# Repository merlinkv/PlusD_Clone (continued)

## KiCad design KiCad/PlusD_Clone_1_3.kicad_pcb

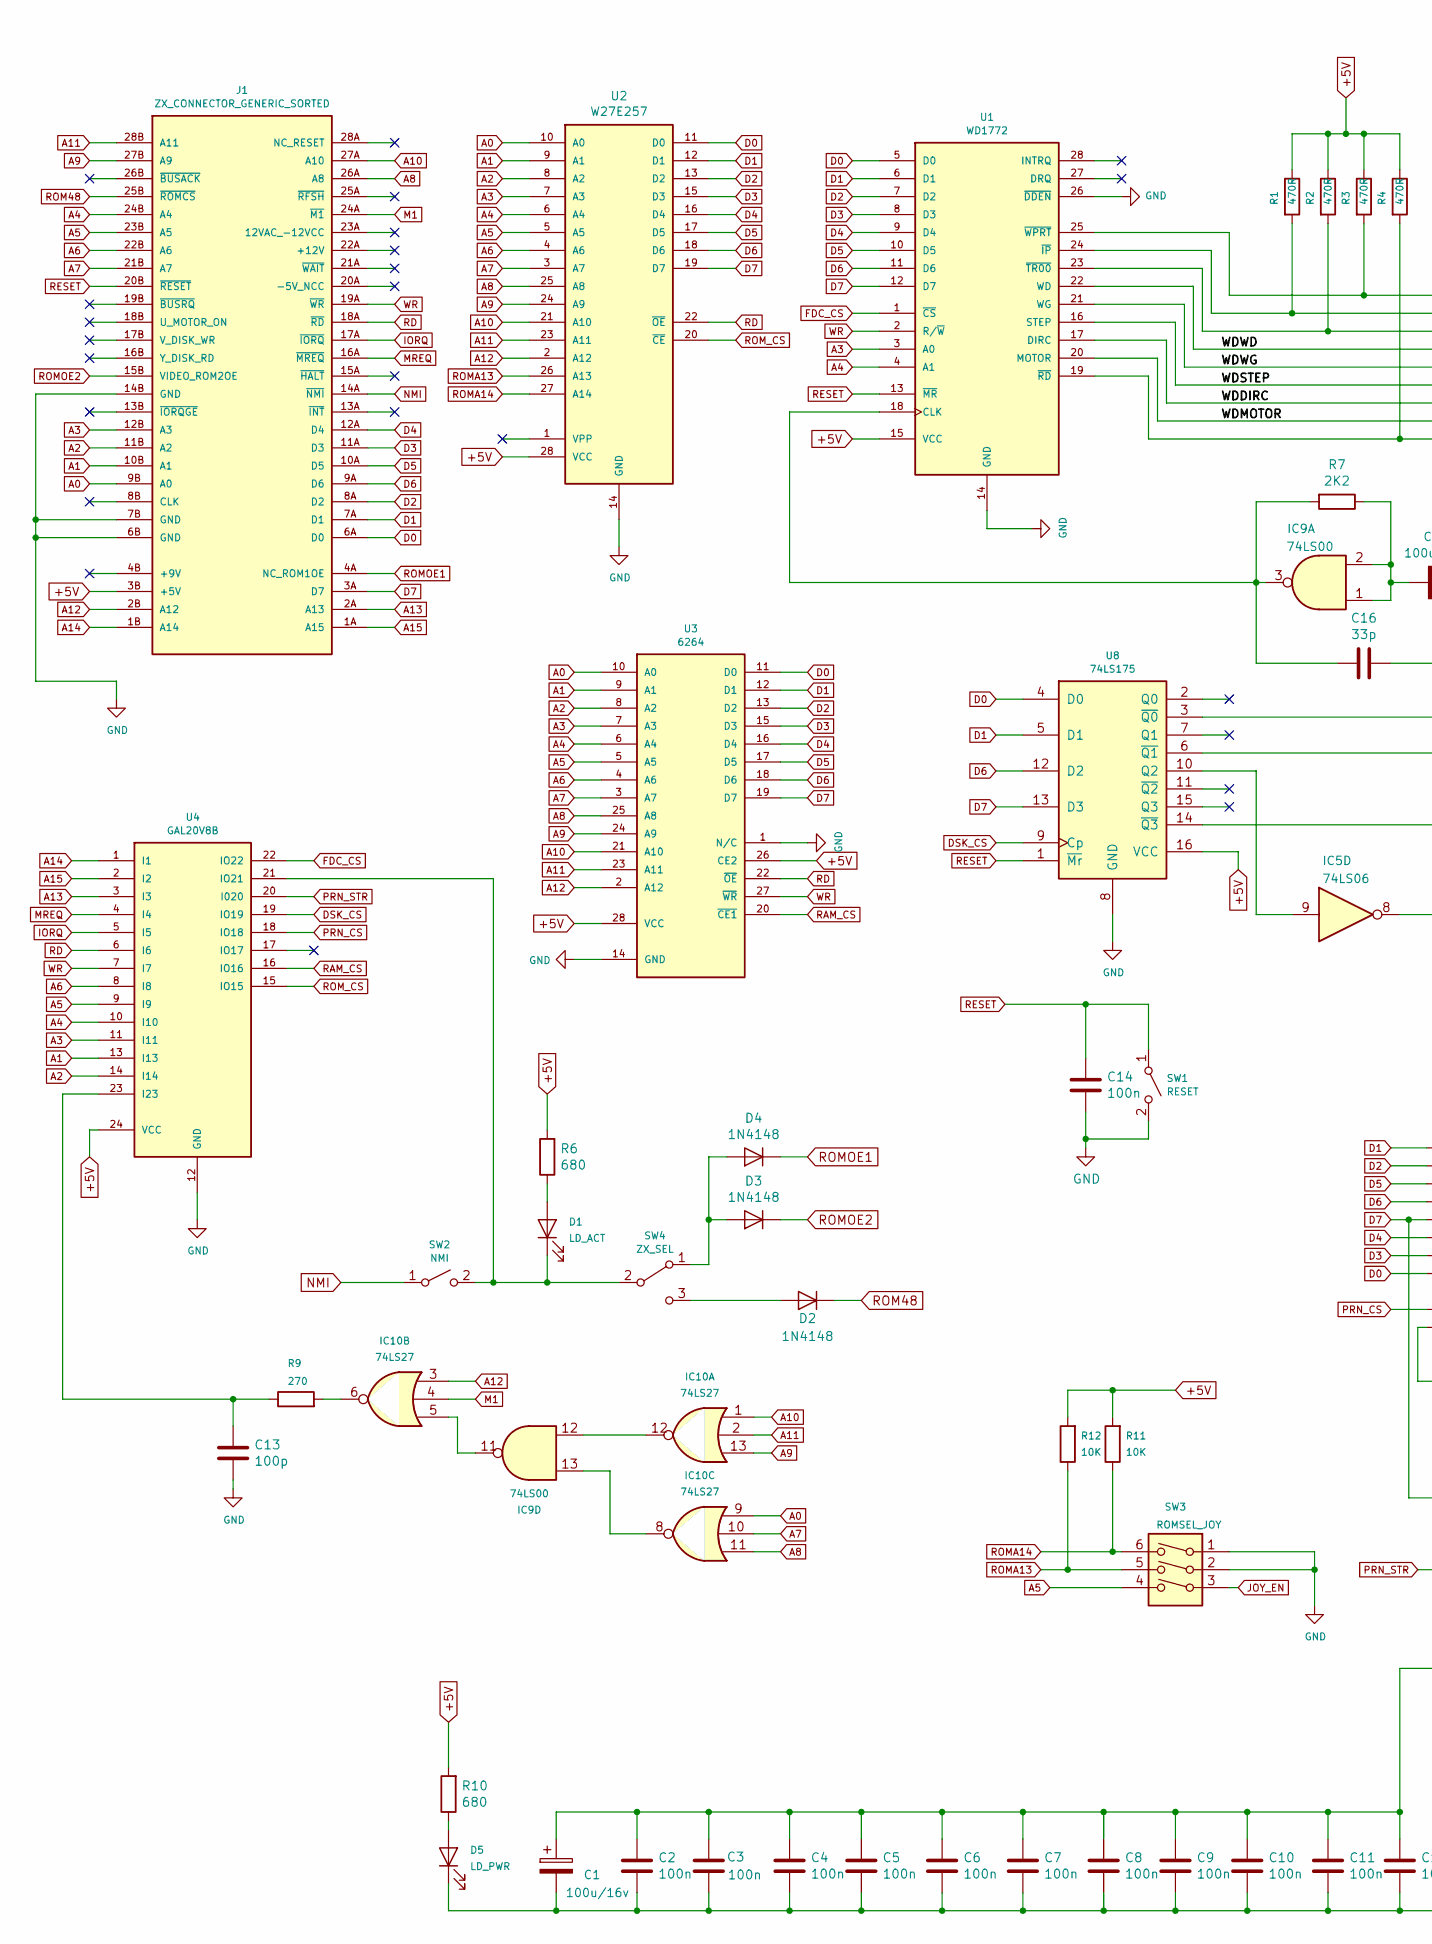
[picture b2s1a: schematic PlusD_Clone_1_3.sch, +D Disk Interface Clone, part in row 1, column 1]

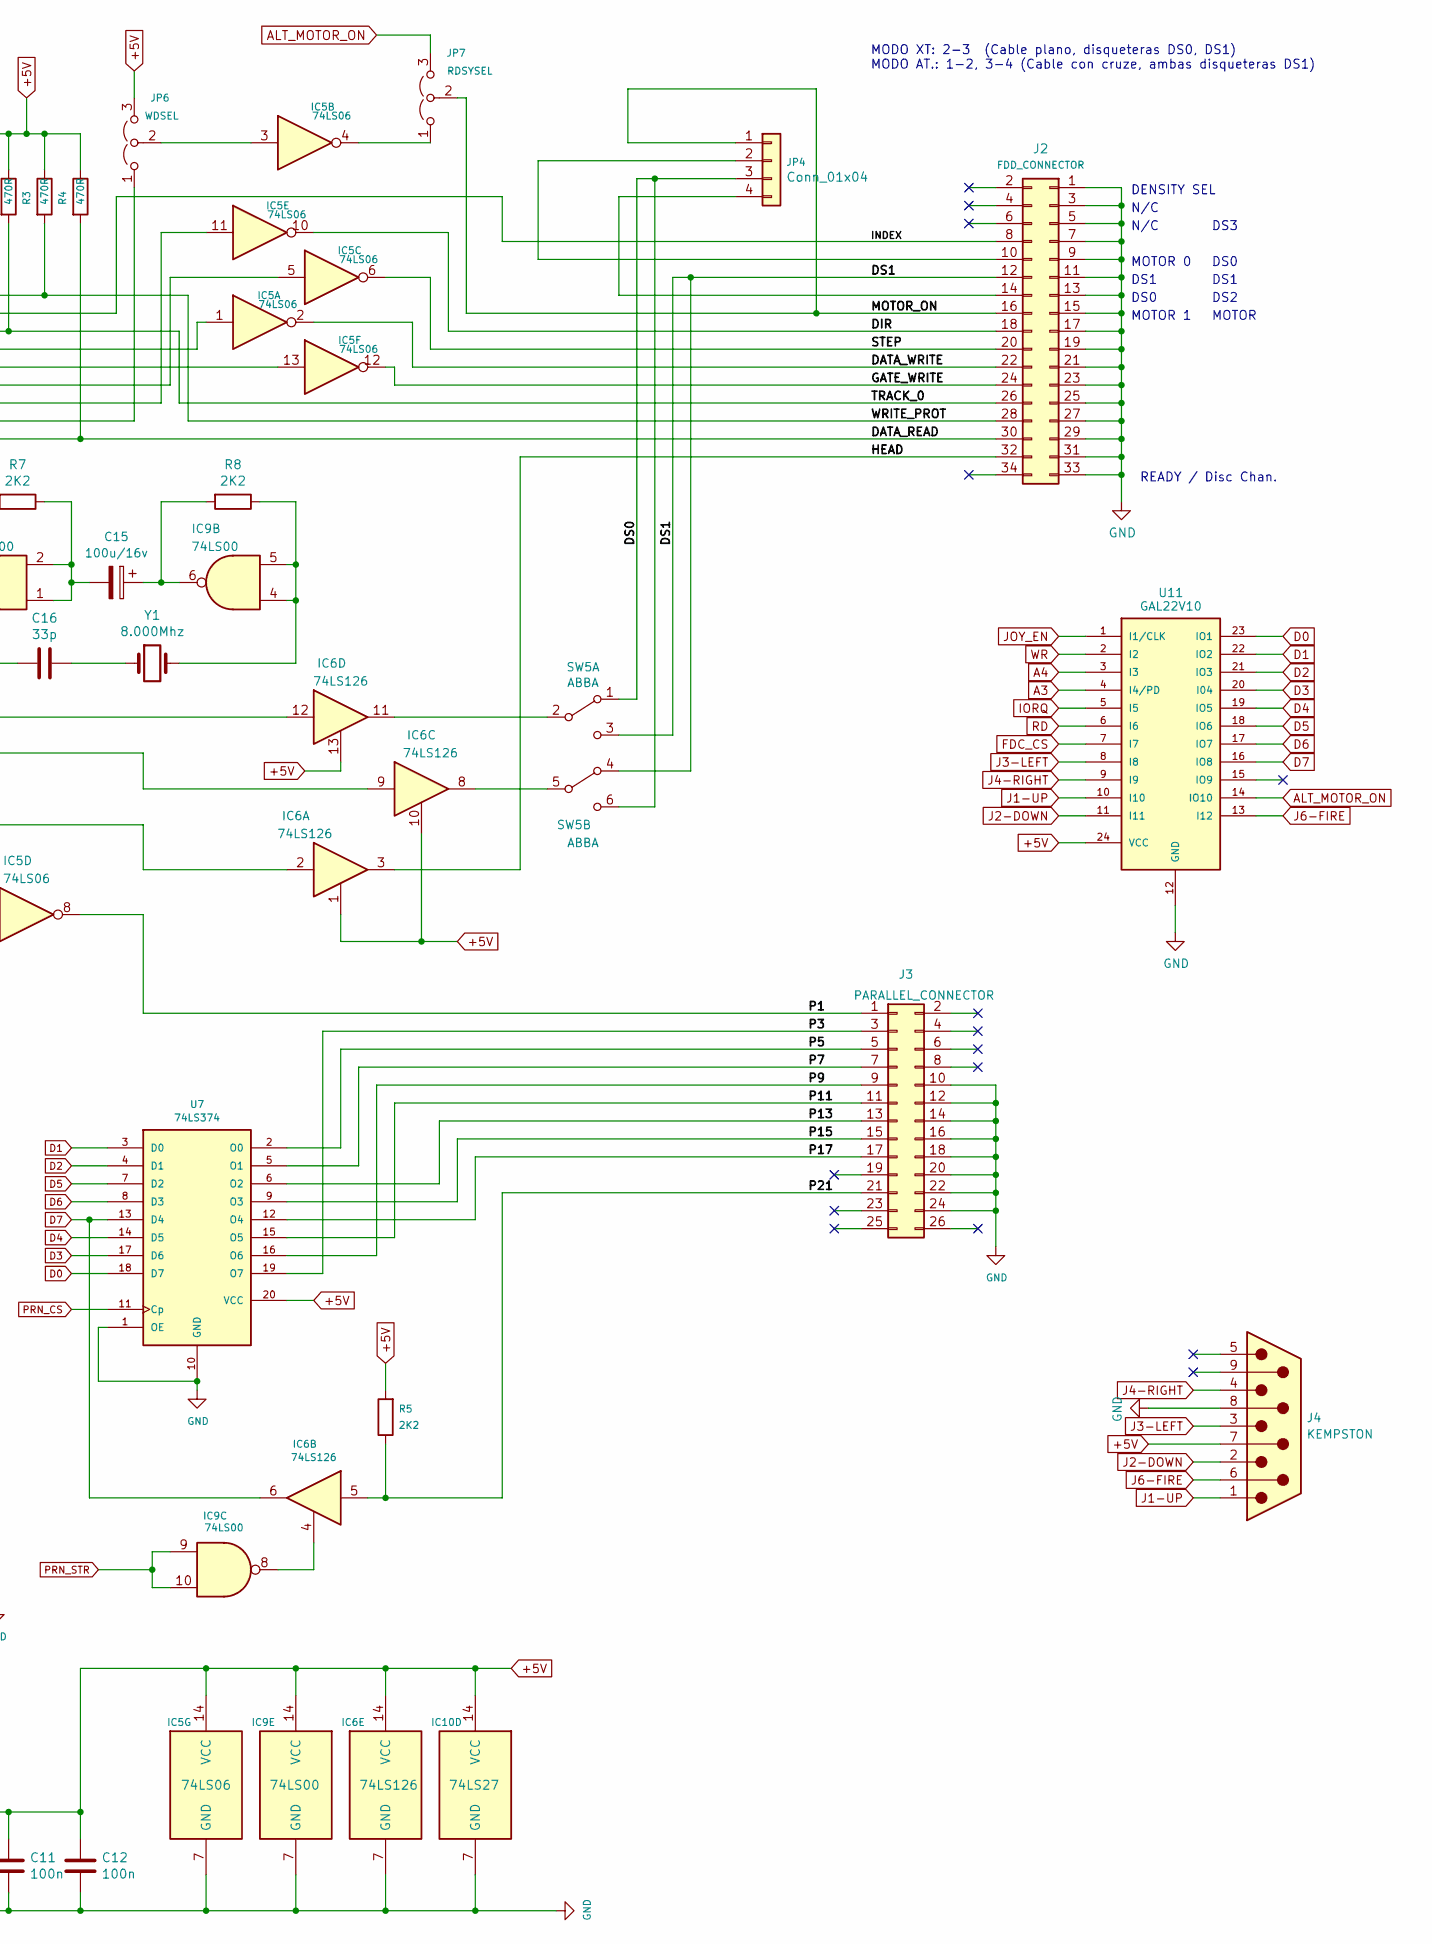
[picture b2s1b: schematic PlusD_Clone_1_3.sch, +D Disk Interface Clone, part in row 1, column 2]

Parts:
C1, C15: 100u/16v; C_Elec_6.3x5.4
C2, C3, C4, C5, C6, C7, C8, C9, C10, C11, C12, C14: 100n; C_Disc_D5.0mm_W2.5mm_P5.00mm
C13: 100p; C_Disc_D5.0mm_W2.5mm_P5.00mm
C16: 33p; C_Disc_D5.0mm_W2.5mm_P5.00mm
D1: LD_ACT; LED_D5.0mm
D2, D3, D4: 1N4148; D_DO-35_SOD27_P7.62mm_Horizontal
D5: LD_PWR; LED_D5.0mm
IC5: 74LS06; DIP-14_W7.62mm_Socket_LongPads
IC6: 74LS126; DIP-14_W7.62mm_Socket_LongPads
IC9: 74LS00; DIP-14_W7.62mm_Socket_LongPads
IC10: 74LS27; DIP-14_W7.62mm_Socket_LongPads
J1: ZX_CONNECTOR_GENERIC_SORTED
J2: FDD_CONNECTOR; PinHeader_2x17_P2.54mm_Vertical
J3: PARALLEL_CONNECTOR; PinHeader_2x13_P2.54mm_Vertical
J4: KEMPSTON; DSUB-9_Male_Horizontal_P2.77x2.84mm_EdgePinOffset4.94mm_Hou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
JP4: Conn_01x04; PinHeader_1x04_P2.54mm_Horizontal
JP6: WDSEL; SolderJumper-3_P1.3mm_Open_RoundedPad1.0x1.5mm
JP7: RDSYSEL; SolderJumper-3_P1.3mm_Open_RoundedPad1.0x1.5mm
R1, R2, R3, R4: 470R; R_Axial_DIN0207_L6.3mm_D2.5mm_P7.62mm_Horizontal
R5, R7, R8: 2K2; R_Axial_DIN0207_L6.3mm_D2.5mm_P7.62mm_Horizontal
R6, R10: 680; R_Axial_DIN0207_L6.3mm_D2.5mm_P7.62mm_Horizontal
R9: 270; R_Axial_DIN0207_L6.3mm_D2.5mm_P7.62mm_Horizontal
R11, R12: 10K; R_Axial_DIN0207_L6.3mm_D2.5mm_P7.62mm_Horizontal
SW1: RESET; SW_PUSH_6mm
SW2: NMI; SW_PUSH_6mm
SW3: ROMSEL_JOY; SW_DIP_SPSTx03_Piano_10.8x9.18mm_W7.62mm_P2.54mm
SW4: ZX_SEL; SW_CuK_OS102011MA1QN1_SPDT_Angled
SW5: ABBA; SW_CuK_JS202011AQN_DPDT_Angled
U1: WD1772; DIP-28_W15.24mm_Socket_LongPads
U2: W27E257; DIP-28_W15.24mm_Socket_LongPads
U3: 6264; DIP-28_W15.24mm_Socket_LongPads
U4: GAL20V8B; DIP-24_W7.62mm_Socket_LongPads
U7: 74LS374; DIP-20_W7.62mm_Socket_LongPads
U8: 74LS175; DIP-16_W7.62mm_Socket_LongPads
U11: GAL22V10; DIP-24_W7.62mm_Socket_LongPads
Y1: 8.000Mhz; Crystal_HC18-U_Vertical

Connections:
+5V: C1.1, C2.2, C3.2, C4.2, C5.2, C6.2, C7.2, C8.2, C9.2, C10.2, C11.2, C12.2, IC5.14 (VCC), IC6.1, IC6.10, IC6.13, IC6.14 (VCC), IC9.14 (VCC), IC10.14 (VCC), J1.3B (+5V), J4.7, JP6.3 (B), R1.1, R2.1, R3.1, R4.1, R5.2, R6.2, R10.2, R11.2, R12.2, U1.15 (VCC), U2.28 (VCC), U3.26 (CE2), U3.28 (VCC), U4.24 (VCC), U7.20 (VCC), U8.16 (VCC), U11.24 (VCC)
/DATA_READ: J2.30, R4.2, U1.19 (~RD)
/DATA_WRITE: IC5.2, J2.22
/DIR: IC5.10, J2.18
/DS0: JP4.3, SW5.1 (A), SW5.6 (C)
/DS1: J2.12, SW5.3 (C), SW5.4 (A)
/GATE_WRITE: IC5.12, J2.24
/HEAD: IC6.3, J2.32
/INDEX: J2.8, R1.2, U1.24 (~IP)
/MOTOR_ON: J2.16, JP4.1, JP7.2 (C)
/P1: IC5.8, J3.1
/P3: J3.3, U7.19 (O7)
/P5: J3.5, U7.2 (O0)
/P7: J3.7, U7.5 (O1)
/P9: J3.9, U7.16 (O6)
/P11: J3.11, U7.15 (O5)
/P13: J3.13, U7.6 (O2)
/P15: J3.15, U7.9 (O3)
/P17: J3.17, U7.12 (O4)
/P21: IC6.5, J3.21, R5.1
/STEP: IC5.6, J2.20
/TRACK_0: J2.26, R2.2, U1.23 (~TR00)
/WDDIRC: IC5.11, U1.17 (DIRC)
/WDMOTOR: JP6.1 (A), U1.20 (MOTOR)
/WDSTEP: IC5.5, U1.16 (STEP)
/WDWD: IC5.1, U1.22 (WD)
/WDWG: IC5.13, U1.21 (WG)
/WRITE_PROT: J2.28, R3.2, U1.25 (~WPRT)
A0: IC10.9, J1.9B (A0), U2.10 (A0), U3.10 (A0)
A1: J1.10B (A1), U2.9 (A1), U3.9 (A1), U4.13 (I13)
A2: J1.11B (A2), U2.8 (A2), U3.8 (A2), U4.14 (I14)
A3: J1.12B (A3), U1.3 (A0), U2.7 (A3), U3.7 (A3), U4.11 (I11), U11.4 (I4/PD)
A4: J1.24B (A4), U1.4 (A1), U2.6 (A4), U3.6 (A4), U4.10 (I10), U11.3 (I3)
A5: J1.23B (A5), SW3.4, U2.5 (A5), U3.5 (A5), U4.9 (I9)
A6: J1.22B (A6), U2.4 (A6), U3.4 (A6), U4.8 (I8)
A7: IC10.10, J1.21B (A7), U2.3 (A7), U3.3 (A7)
A8: IC10.11, J1.26A (A8), U2.25 (A8), U3.25 (A8)
A9: IC10.13, J1.27B (A9), U2.24 (A9), U3.24 (A9)
A10: IC10.1, J1.27A (A10), U2.21 (A10), U3.21 (A10)
A11: IC10.2, J1.28B (A11), U2.23 (A11), U3.23 (A11)
A12: IC10.3, J1.2B (A12), U2.2 (A12), U3.2 (A12)
A13: J1.2A (A13), U4.3 (I3)
A14: J1.1B (A14), U4.1 (I1)
A15: J1.1A (A15), U4.2 (I2)
ALT_MOTOR_ON: JP7.3 (B), U11.14 (IO10)
D0: J1.6A (D0), U1.5 (D0), U2.11 (D0), U3.11 (D0), U7.18 (D7), U8.4 (D0), U11.23 (IO1)
D1: J1.7A (D1), U1.6 (D1), U2.12 (D1), U3.12 (D1), U7.3 (D0), U8.5 (D1), U11.22 (IO2)
D2: J1.8A (D2), U1.7 (D2), U2.13 (D2), U3.13 (D2), U7.4 (D1), U11.21 (IO3)
D3: J1.11A (D3), U1.8 (D3), U2.15 (D3), U3.15 (D3), U7.17 (D6), U11.20 (I04)
D4: J1.12A (D4), U1.9 (D4), U2.16 (D4), U3.16 (D4), U7.14 (D5), U11.19 (IO5)
D5: J1.10A (D5), U1.10 (D5), U2.17 (D5), U3.17 (D5), U7.7 (D2), U11.18 (IO6)
D6: J1.9A (D6), U1.11 (D6), U2.18 (D6), U3.18 (D6), U7.8 (D3), U8.12 (D2), U11.17 (IO7)
D7: IC6.6, J1.3A (D7), U1.12 (D7), U2.19 (D7), U3.19 (D7), U7.13 (D4), U8.13 (D3), U11.16 (IO8)
DSK_CS: U4.19 (IO19), U8.9 (Cp)
FDC_CS: U1.1 (~CS), U4.22 (IO22), U11.7 (I7)
GND: C1.2, C2.1, C3.1, C4.1, C5.1, C6.1, C7.1, C8.1, C9.1, C10.1, C11.1, C12.1, C13.1, C14.1, D5.1 (K), IC5.7 (GND), IC6.7 (GND), IC9.7 (GND), IC10.7 (GND), J1.6B (GND), J1.7B (GND), J1.14B (GND), J2.1, J2.3, J2.5, J2.7, J2.9, J2.11, J2.13, J2.15, J2.17, J2.19, J2.21, J2.23, J2.25, J2.27, J2.29, J2.31, J2.33, J3.10, J3.12, J3.14, J3.16, J3.18, J3.20, J3.22, J3.24, J4.8, SW1.2 (B), SW3.1, SW3.2, U1.14 (GND), U1.26 (~DDEN), U2.14 (GND), U3.1 (N/C), U3.14 (GND), U4.12 (GND), U7.1 (OE), U7.10 (GND), U8.8 (GND), U11.12 (GND)
IORQ: J1.17A (~IORQ), U4.5 (I5), U11.5 (I5)
J1-UP: J4.1, U11.10 (I10)
J2-DOWN: J4.2, U11.11 (I11)
J3-LEFT: J4.3, U11.8 (I8)
J4-RIGHT: J4.4, U11.9 (I9)
J6-FIRE: J4.6, U11.13 (I12)
JOY_EN: SW3.3, U11.1 (I1/CLK)
M1: IC10.4, J1.24A (~M1)
MREQ: J1.16A (~MREQ), U4.4 (I4)
NMI: J1.14A (~NMI), SW2.1 (A)
unnamed: C13.2, R9.1, U4.23 (I23)
unnamed: C15.1, IC9.6, R8.2
unnamed: C15.2, IC9.1, IC9.2, R7.1
unnamed: C16.1, Y1.1
unnamed: C16.2, IC9.3, R7.2, U1.18 (CLK)
unnamed: D1.1 (K), SW2.2 (B), SW4.2 (B), U4.21 (IO21)
unnamed: D1.2 (A), R6.1
unnamed: D2.2 (A), SW4.3 (C)
unnamed: D3.2 (A), D4.2 (A), SW4.1 (A)
unnamed: D5.2 (A), R10.1
unnamed: IC5.3, JP6.2 (C)
unnamed: IC5.4, JP7.1 (A)
unnamed: IC5.9, U8.10 (Q2)
unnamed: IC6.2, U8.14 (~Q3)
unnamed: IC6.4, IC9.8
unnamed: IC6.8, SW5.5 (B)
unnamed: IC6.9, U8.6 (~Q1)
unnamed: IC6.11, SW5.2 (B)
unnamed: IC6.12, U8.3 (~Q0)
unnamed: IC9.4, IC9.5, R8.1, Y1.2
unnamed: IC9.11, IC10.5
unnamed: IC10.6, R9.2
unnamed: IC9.13, IC10.8
unnamed: IC9.12, IC10.12
unnamed: J2.10, JP4.2
unnamed: J2.14, JP4.4
PRN_CS: U4.18 (IO18), U7.11 (Cp)
PRN_STR: IC9.9, IC9.10, U4.20 (I020)
RAM_CS: U3.20 (~CE1), U4.16 (IO16)
RD: J1.18A (~RD), U2.22 (~OE), U3.22 (~OE), U4.6 (I6), U11.6 (I6)
RESET: C14.2, J1.20B (~RESET), SW1.1 (A), U1.13 (~MR), U8.1 (~Mr)
ROM48: D2.1 (K), J1.25B (~ROMCS)
ROMA13: R12.1, SW3.5, U2.26 (A13)
ROMA14: R11.1, SW3.6, U2.27 (A14)
ROMOE1: D4.1 (K), J1.4A (NC_ROM1OE)
ROMOE2: D3.1 (K), J1.15B (VIDEO_ROM2OE)
ROM_CS: U2.20 (~CE), U4.15 (IO15)
WR: J1.19A (~WR), U1.2 (R/~W), U3.27 (~WR), U4.7 (I7), U11.2 (I2)

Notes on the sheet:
READY / Disc Chan.
DENSITY SEL
N/C
MOTOR 1
DS0
DS1
MOTOR 0
MOTOR
DS2
DS0
DS3
MODO XT: 2-3 (Cable plano, disqueteras DS0, DS1) MODO AT.: 1-2, 3-4 (Cable con cruze, ambas disqueteras DS1)

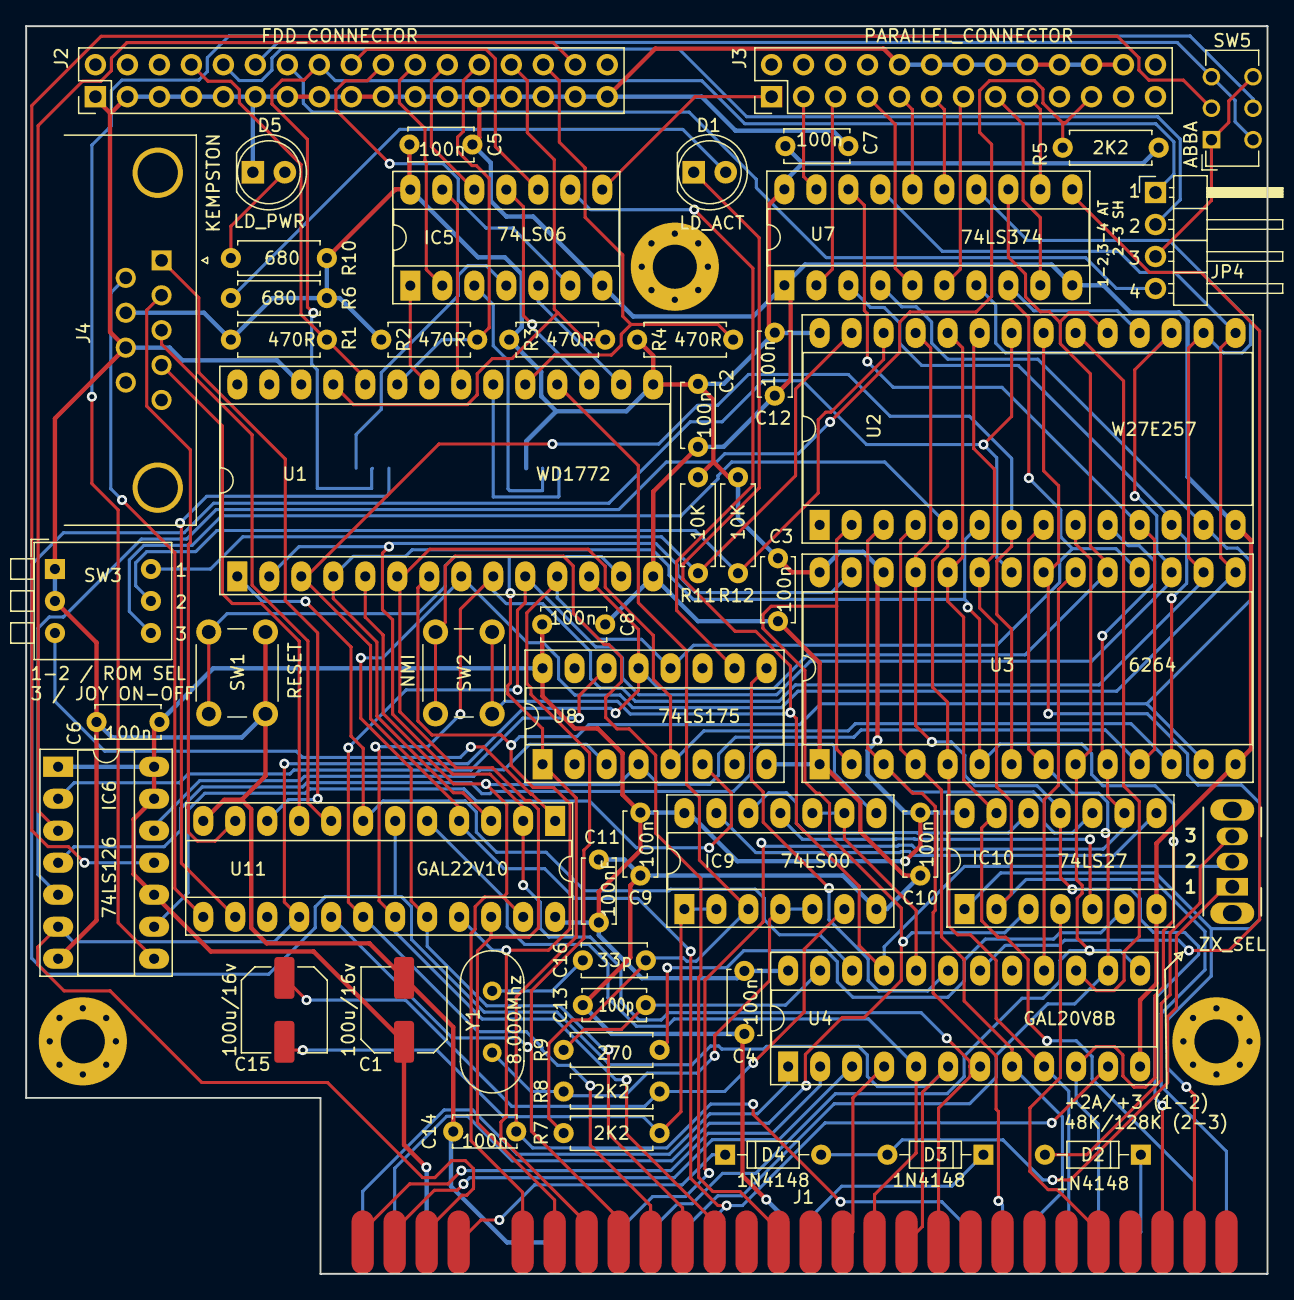
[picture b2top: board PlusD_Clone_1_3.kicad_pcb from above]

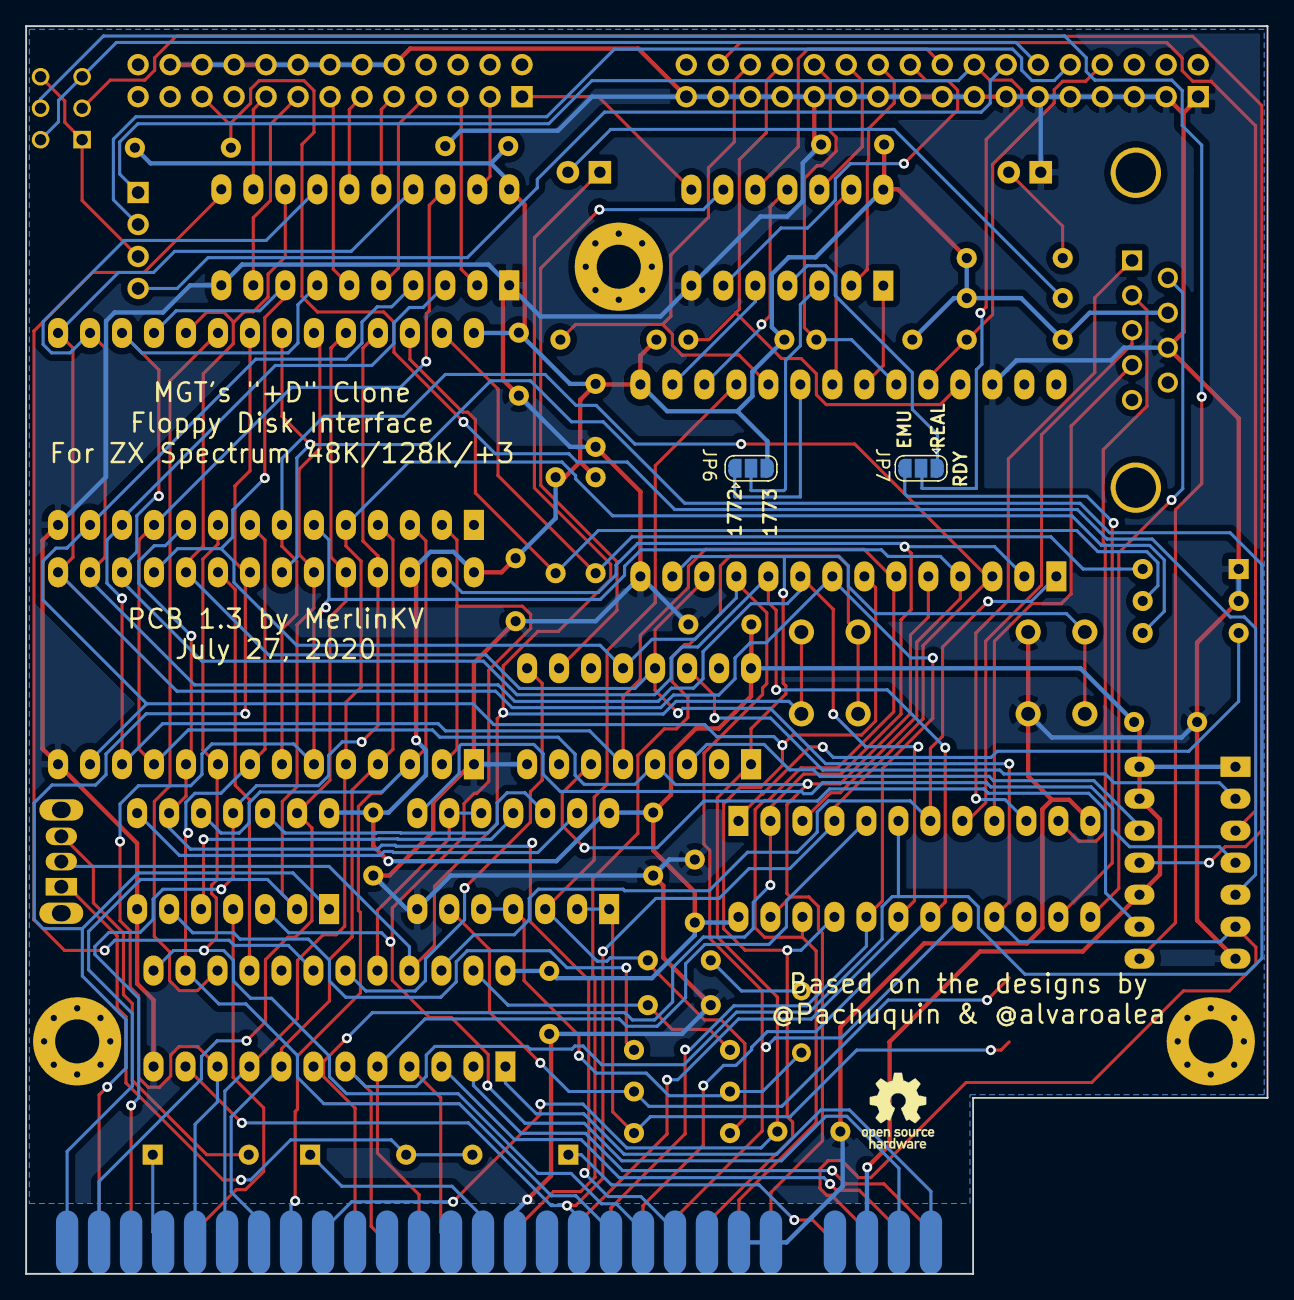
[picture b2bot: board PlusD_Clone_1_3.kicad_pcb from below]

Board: 2 copper layers, 98.6 x 99.1 mm, 61 parts (3 on the bottom side), 104 nets.

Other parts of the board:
HOLE1, HOLE2, HOLE3: MountingHole_3.5mm_Pad_Via
LOGO1: OSHW-Logo_5.7x6mm_SilkScreen

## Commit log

2020-07-07 Create test
